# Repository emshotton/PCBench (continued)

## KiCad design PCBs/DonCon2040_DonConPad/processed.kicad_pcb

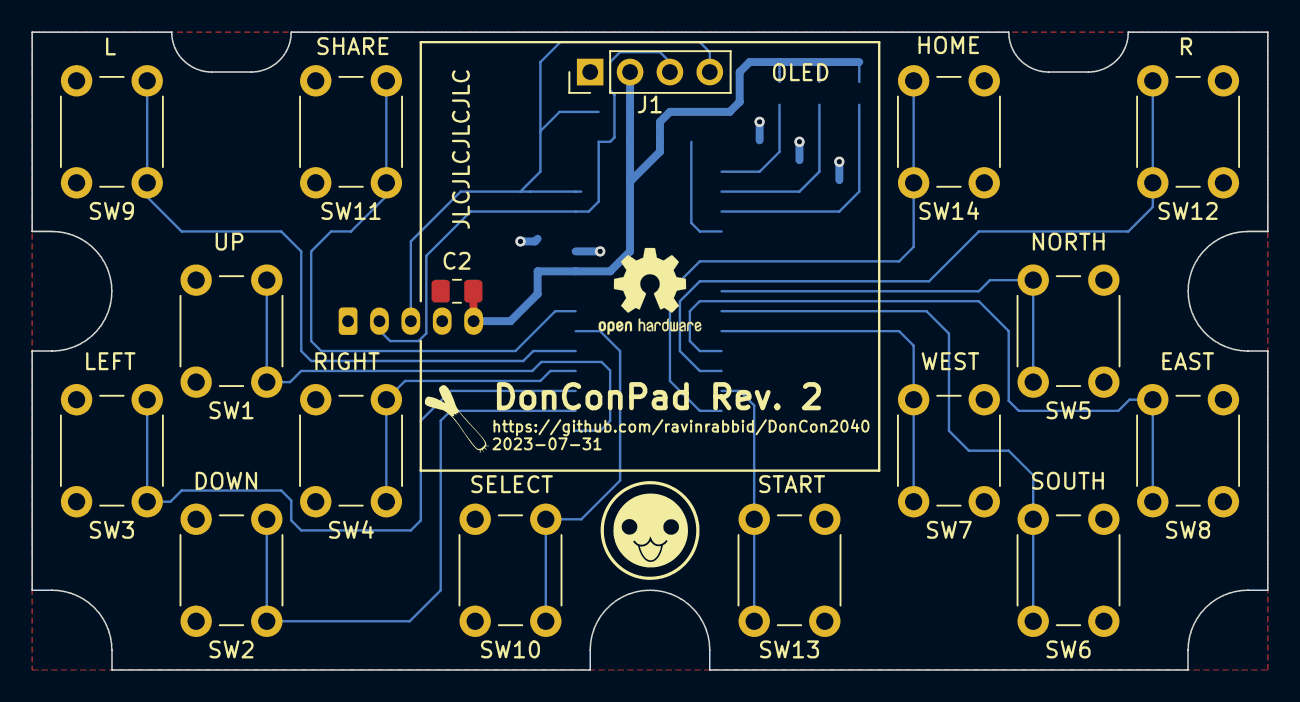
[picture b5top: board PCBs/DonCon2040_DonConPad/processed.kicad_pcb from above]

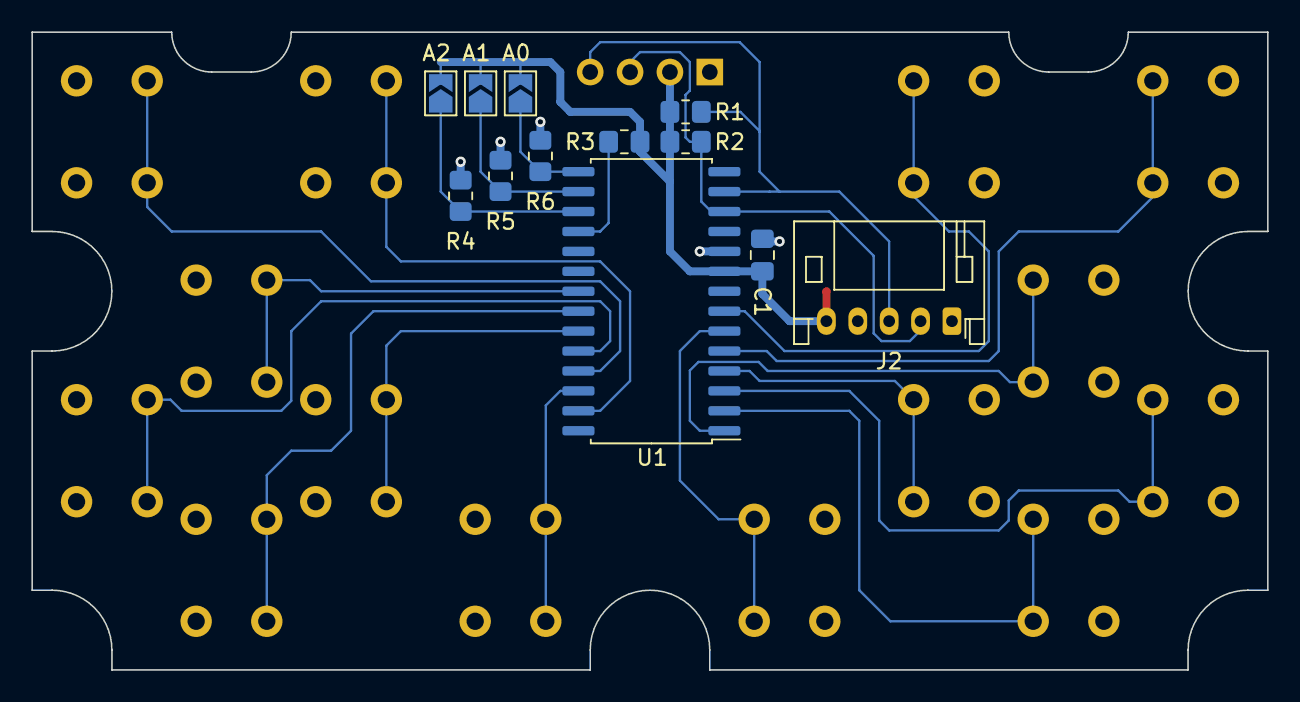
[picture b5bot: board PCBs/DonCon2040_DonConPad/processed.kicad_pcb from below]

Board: 2 copper layers, 78.7 x 40.6 mm, 31 parts (12 on the bottom side), 22 nets.

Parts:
C1: 0.1uF; C_0805_2012Metric_Pad1.18x1.45mm_HandSolder
C2: 10uF; C_0805_2012Metric_Pad1.18x1.45mm_HandSolder
J1: Display; PinHeader_1x04_P2.54mm_Vertical
J2: Host; JST_PH_S5B-PH-K_1x05_P2.00mm_Horizontal
JP1: A0; SolderJumper-2_P1.3mm_Open_TrianglePad1.0x1.5mm
JP2: A1; SolderJumper-2_P1.3mm_Open_TrianglePad1.0x1.5mm
JP3: A2; SolderJumper-2_P1.3mm_Open_TrianglePad1.0x1.5mm
LOGO1: OSHW-Logo2_7.3x6mm_SilkScreen
LOGO2: LOGO; Leek-Logo_6.3mm_Silkscreen
LOGO3: Donchan-Logo_6.3mm_Silkscreen
R1, R2, R3, R4, R5, R6: 10k; R_0805_2012Metric_Pad1.20x1.40mm_HandSolder
SW1: Up; SW_PUSH_6mm_H5mm
SW2: Down; SW_PUSH_6mm_H5mm
SW3: Left; SW_PUSH_6mm_H5mm
SW4: Right; SW_PUSH_6mm_H5mm
SW5: North; SW_PUSH_6mm_H5mm
SW6: South; SW_PUSH_6mm_H5mm
SW7: West; SW_PUSH_6mm_H5mm
SW8: East; SW_PUSH_6mm_H5mm
SW9: L; SW_PUSH_6mm_H5mm
SW10: Select; SW_PUSH_6mm_H5mm
SW11: Share; SW_PUSH_6mm_H5mm
SW12: R; SW_PUSH_6mm_H5mm
SW13: Start; SW_PUSH_6mm_H5mm
SW14: Home; SW_PUSH_6mm_H5mm
U1: MCP23017_SO; SOIC-28W_7.5x17.9mm_P1.27mm

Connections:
+3V3: C1.2, C2.2, J1.2, J2.5, JP1.2 (B), JP2.2 (B), JP3.2 (B), R1.1, R2.1, R3.1, U1.9 (VDD)
GND: C1.1, C2.1, J1.1, J2.1, J2.4, R4.2, R5.2, R6.2, SW1.2, SW2.2, SW3.2, SW4.2, SW5.2, SW6.2, SW7.2, SW8.2, SW9.2, SW10.2, SW11.2, SW12.2, SW13.2, SW14.2, U1.10 (VSS)
unnamed: JP1.1 (A), R6.1, U1.15 (A0)
unnamed: JP2.1 (A), R5.1, U1.16 (A1)
unnamed: JP3.1 (A), R4.1, U1.17 (A2)
unnamed: SW5.1, U1.21 (GPA0)
unnamed: SW6.1, U1.22 (GPA1)
unnamed: SW7.1, U1.23 (GPA2)
unnamed: SW8.1, U1.24 (GPA3)
unnamed: SW12.1, U1.25 (GPA4)
unnamed: SW13.1, U1.26 (GPA5)
unnamed: SW14.1, U1.27 (GPA6)
unnamed: SW1.1, U1.1 (GPB0)
unnamed: SW2.1, U1.2 (GPB1)
unnamed: SW3.1, U1.3 (GPB2)
unnamed: SW4.1, U1.4 (GPB3)
unnamed: SW9.1, U1.5 (GPB4)
unnamed: SW10.1, U1.6 (GPB5)
unnamed: SW11.1, U1.7 (GPB6)
unnamed: R3.2, U1.18 (~RESET)
SCL: J1.3, J2.2, R2.2, U1.12 (SCK)
SDA: J1.4, J2.3, R1.2, U1.13 (SDA)

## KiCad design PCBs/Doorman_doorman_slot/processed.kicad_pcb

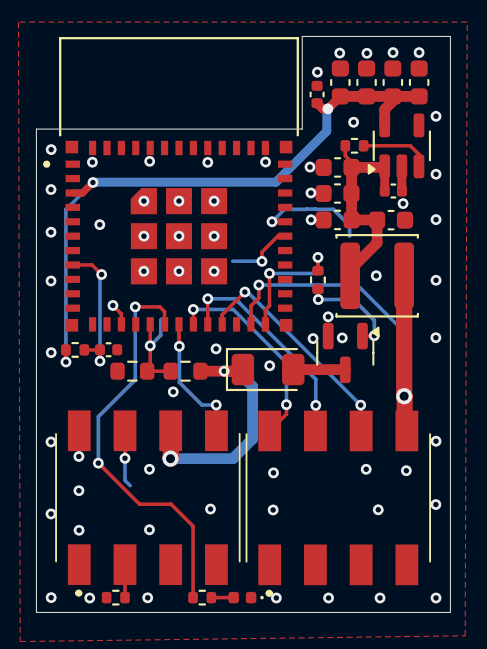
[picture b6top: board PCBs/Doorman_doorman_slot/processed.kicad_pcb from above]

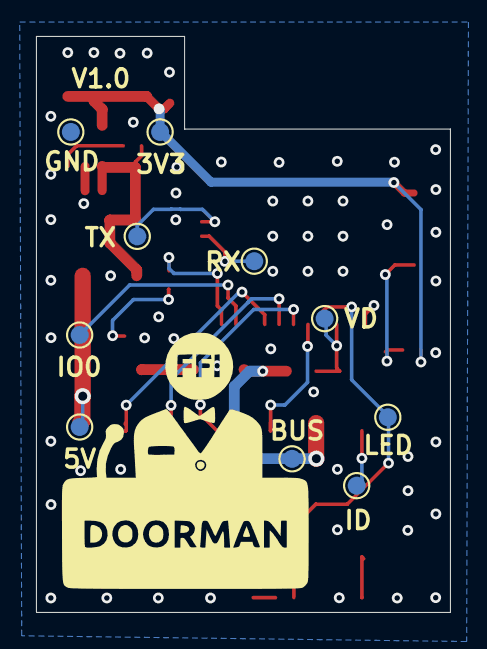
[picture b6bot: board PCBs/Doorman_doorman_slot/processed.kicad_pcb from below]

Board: 4 copper layers, 23.0 x 32.0 mm, 36 parts (10 on the bottom side), 22 nets.

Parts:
C1, C2, C3, C4, C6, C7, C8, C9: 20uF; C_0603_1608Metric
C5, C11: 100nF; C_0402_1005Metric
C10: 20uF; C_0402_1005Metric
D1: Red; LED_0402_1005Metric
D2: D_Zener; D_1206_3216Metric
J2, J3: 70AAJ-4-M0; 70AAJ4M0
L1: TBD; L_APV_ANR4010
Q1: BC817; SOT-23
R1: 2.2K; R_0402_1005Metric
R3, R5: 10K; R_0402_1005Metric
R6: 600; R_0402_1005Metric
R7: 1M; R_0603_1608Metric
R8: 160K; R_0603_1608Metric
R9: 1K; R_0402_1005Metric
TP1: RX TestPoint; TestPoint_Pad_D1.0mm
TP2: TX TestPoint; TestPoint_Pad_D1.0mm
TP3: 3.3V TestPoint; TestPoint_Pad_D1.0mm
TP4: 5V TestPoint; TestPoint_Pad_D1.0mm
TP5: LED TestPoint; TestPoint_Pad_D1.0mm
TP6: Identity TestPoint; TestPoint_Pad_D1.0mm
TP7: VD TestPoint; TestPoint_Pad_D1.0mm
TP8: BUS TestPoint; TestPoint_Pad_D1.0mm
TP9: GND TestPoint; TestPoint_Pad_D1.0mm
TP10: GPIO0 TestPoint; TestPoint_Pad_D1.0mm
U2: XC6210B332MR; SOT-23-5
U3: ESP32-PICO-MINI-02; MODULE_ESP32-PICO-MINI-02

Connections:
+3.3V: C6.1, C7.1, C8.1, C9.1, C10.1, R5.1, TP3.1, U2.5 (VOUT), U3.3 (3V3)
+5V: J3.5, L1.1, TP4.1
GND: C1.1, C2.2, C3.2, C4.2, C5.1, C6.2, C7.2, C8.2, C9.2, C10.2, C11.1, D1.1 (K), J2.1, J2.8, Q1.2 (E), R1.1, R8.1, TP9.1, U2.2 (GND), U3.1 (GND), U3.2 (GND), U3.11 (GND), U3.14 (GND), U3.36 (GND), U3.37 (GND), U3.38 (GND), U3.39 (GND), U3.40 (GND), U3.41 (GND), U3.42 (GND), U3.43 (GND), U3.44 (GND), U3.45 (GND), U3.46 (GND), U3.47 (GND), U3.48 (GND), U3.49 (GND), U3.50 (GND), U3.51 (GND), U3.52 (GND), U3.53 (GND), U3.54 (GND), U3.55 (GND), U3.56 (GND), U3.57 (GND), U3.58 (GND), U3.59 (GND), U3.60 (GND), U3.61 (GND)
GPIO0: TP10.1, U3.23 (IO0)
GPIO4: R9.1, U3.24 (IO4)
GPIO12: J3.8, U3.19 (IO12)
GPIO13: J3.7, U3.20 (IO13)
GPIO14: J2.5, U3.18 (IO14)
GPIO15: J3.6, U3.21 (IO15)
GPIO26: R7.2, R8.2, TP7.1, U3.16 (IO26)
GPIO27: R6.2, TP5.1, U3.17 (IO27)
IDENTITY: J2.2, R1.2
unnamed: D1.2 (A), R6.1
unnamed: D2.2 (A), Q1.3 (C)
unnamed: J2.7, TP6.1
unnamed: Q1.1 (B), R9.2
unnamed: R3.2, U2.3 (CE)
unnamed: C1.2, C2.1, C3.1, C4.1, C5.2, L1.2, R3.1, U2.1 (VIN)
unnamed: C11.2, R5.2, U3.8 (EN)
RX: TP2.1, U3.30 (RXD0)
TASTA_ONLY_BUS: D2.1 (K), J2.6, R7.1, TP8.1
TX: TP1.1, U3.31 (TXD0)

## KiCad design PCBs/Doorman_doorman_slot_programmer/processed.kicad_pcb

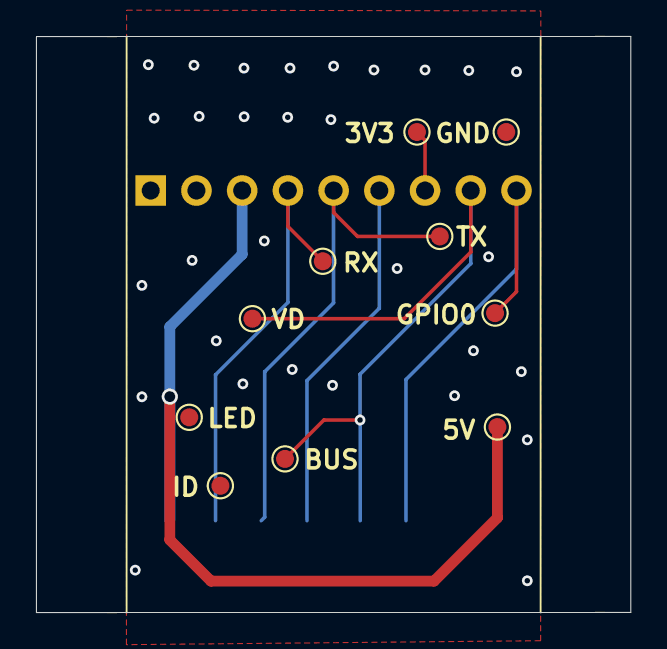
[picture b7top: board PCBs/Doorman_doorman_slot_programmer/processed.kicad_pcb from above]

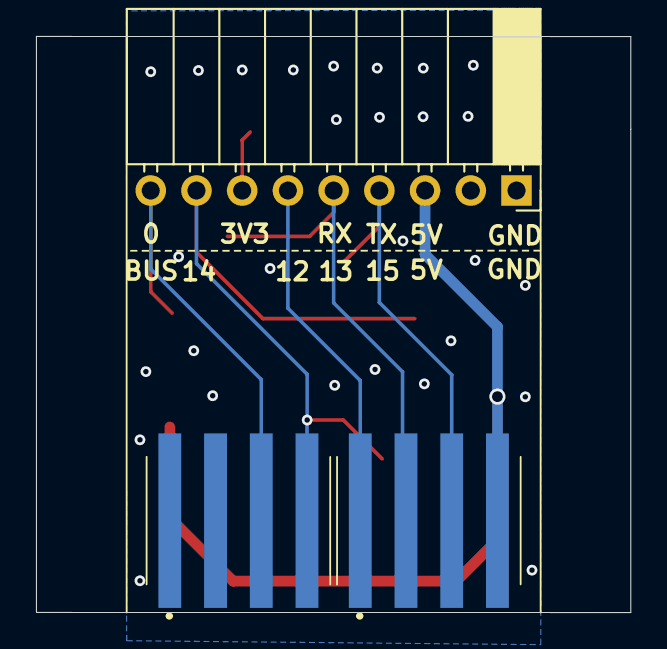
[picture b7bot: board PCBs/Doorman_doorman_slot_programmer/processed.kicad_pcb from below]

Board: 4 copper layers, 33.0 x 32.0 mm, 13 parts (3 on the bottom side), 8 nets.

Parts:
J1: Conn_01x06_Socket; PinSocket_1x09_P2.54mm_Horizontal
J2, J3: 70AAJ-4-M0; 70AAJ4M0
TP1: RX TestPoint; TestPoint_Pad_D1.0mm
TP2: TX TestPoint; TestPoint_Pad_D1.0mm
TP3: 3.3V TestPoint; TestPoint_Pad_D1.0mm
TP4: 5V TestPoint; TestPoint_Pad_D1.0mm
TP5: LED TestPoint; TestPoint_Pad_D1.0mm
TP6: Identity TestPoint; TestPoint_Pad_D1.0mm
TP7: VD TestPoint; TestPoint_Pad_D1.0mm
TP8: BUS TestPoint; TestPoint_Pad_D1.0mm
TP9: GND TestPoint; TestPoint_Pad_D1.0mm
TP10: GPIO0 TestPoint; TestPoint_Pad_D1.0mm

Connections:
+3.3V: J1.7, TP3.1
+5V: J1.3, J2.4, TP4.1
GND: J1.1, J3.1, TP9.1
GPIO0: J1.9, J3.3, TP10.1
PIN5: J1.6, J2.1
RX: J1.5, J2.2, TP1.1
TASTA_ONLY_BUS: J1.8, J3.4, TP7.1, TP8.1
TX: J1.4, J2.3, TP2.1
